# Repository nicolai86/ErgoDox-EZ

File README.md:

# ErgoDox-EZ

[ErgoDox EZ](https://ergodox-ez.com/) LED mod to convert your regular ErgoDox EZ into an ErgoDox EZ shine.  
The total cost for this mod is about about 40 CAD (~30 CAD for PCBs, ~10 CAD for components)

## Instructions

To build this mod you need to assemble two LED strips, and one I2C bridge. The LED strips are installed on both sides. The right hand LED strip is directly connected to the main PCB. The left hand LED strip requires an I2C bridge to function.

## Firmware

Once you've connected your Atmega168 you can compile the firmware and flash your microcontroller with the included makefile:

```
$ make build
$ make flash
```

The makefile is setup to use the AVR ISP MKII.

## LED strip

You will need to LED pcbs to build this mod. The LED strips are identical for both sides.

### List of materials

| Component | Amount        | Notes |
|-----------|:-------------:|------:|
| RGBW6812  | 30            | 15 per side; Can be ordered at Aliexpress |
| 3-pin micro JST connector | 1 | right hand connector to main PCB |

The gerber files, eagle project schematics and board files are included in the led-strip folder.

### Assembly

The LED strip assembly needs to be done twice, once for each half. For each side:

1. Solder all 15 RGBW SK6812 LEDs 
2. Solder the cables according to the marks

For the right hand you can solder the cables to the keyboard, or use a 3-pin micro JST connector instead.
The left hand needs to be connected to an I2C bridge:

## I2C bridge

### List of materials

| Component | Amount        | Notes |
|-----------|:-------------:|------:|
| atmega168pa-au  | 1       | Required to decode I2C traffic |
| 0805 22pF cap   | 2       | |
| 0805 10uF cap   | 1       | |
| 0805 10K resistor | 3     | |
| CSM-7X-DU 16Mhz oscillator | 1     | |
| 6 pin AVR ISP connector | 1     | |
| 4-pin micro JST connector | 1 | left hand connector to main PCB |

The gerber files, eagle project schematics and board files are included in the i2c-bride folder.

## Assembly

1. Solder the Atmega168p. Make sure to align the dark circle with the PCB properly. I've used SMD solder paste to place a film over all pins, solder one pin at a time.
2. Solder the 2 22pF caps, C3 and C2.
3. Solder the oscillator. 
4. Solder the 10uF cap.
5. Solder the 3 10k res.
6. Solder the jack. Note that you'll need to desolder it after flashing, or cut them off.

The left hand will look like this after soldering:

check out [KeebTalk](https://www.keebtalk.com/t/did-anybody-try-to-mod-their-ergodox-ez-with-a-custom-led-array/2286) for more images.

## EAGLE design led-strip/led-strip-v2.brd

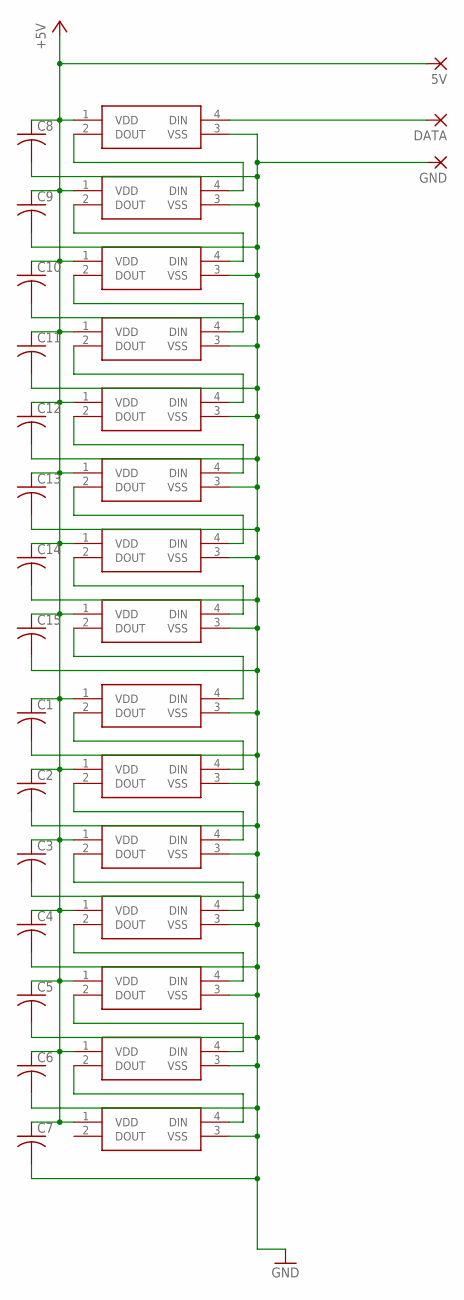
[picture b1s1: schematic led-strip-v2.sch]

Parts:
5V: 1,6/0,8
C1, C2, C3, C4, C5, C6, C7, C8, C9, C10, C11, C12, C13, C14, C15: C-USC0805; C0805
DATA: 1,6/0,8
GND: 1,6/0,8
LED1, LED2, LED3, LED4, LED5, LED6, LED7, LED8, LED9, LED10, LED11, LED12, LED13, LED14, LED15: 1655; WS2812B_1

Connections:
+5V: 5V.1, C1.1, C2.1, C3.1, C4.1, C5.1, C6.1, C7.1, C8.1, C9.1, C10.1, C11.1, C12.1, C13.1, C14.1, C15.1, LED1.1 (VDD), LED2.1 (VDD), LED3.1 (VDD), LED4.1 (VDD), LED5.1 (VDD), LED6.1 (VDD), LED7.1 (VDD), LED8.1 (VDD), LED9.1 (VDD), LED10.1 (VDD), LED11.1 (VDD), LED12.1 (VDD), LED13.1 (VDD), LED14.1 (VDD), LED15.1 (VDD)
DATA-IN: DATA.1, LED1.4 (DIN)
GND: C1.2, C2.2, C3.2, C4.2, C5.2, C6.2, C7.2, C8.2, C9.2, C10.2, C11.2, C12.2, C13.2, C14.2, C15.2, GND.1, LED1.3 (VSS), LED2.3 (VSS), LED3.3 (VSS), LED4.3 (VSS), LED5.3 (VSS), LED6.3 (VSS), LED7.3 (VSS), LED8.3 (VSS), LED9.3 (VSS), LED10.3 (VSS), LED11.3 (VSS), LED12.3 (VSS), LED13.3 (VSS), LED14.3 (VSS), LED15.3 (VSS)
unnamed: LED1.2 (DOUT), LED2.4 (DIN)
unnamed: LED2.2 (DOUT), LED3.4 (DIN)
unnamed: LED3.2 (DOUT), LED4.4 (DIN)
unnamed: LED4.2 (DOUT), LED5.4 (DIN)
unnamed: LED5.2 (DOUT), LED6.4 (DIN)
unnamed: LED6.2 (DOUT), LED7.4 (DIN)
unnamed: LED7.2 (DOUT), LED8.4 (DIN)
unnamed: LED8.2 (DOUT), LED9.4 (DIN)
unnamed: LED9.2 (DOUT), LED10.4 (DIN)
unnamed: LED10.2 (DOUT), LED11.4 (DIN)
unnamed: LED11.2 (DOUT), LED12.4 (DIN)
unnamed: LED12.2 (DOUT), LED13.4 (DIN)
unnamed: LED13.2 (DOUT), LED14.4 (DIN)
unnamed: LED14.2 (DOUT), LED15.4 (DIN)

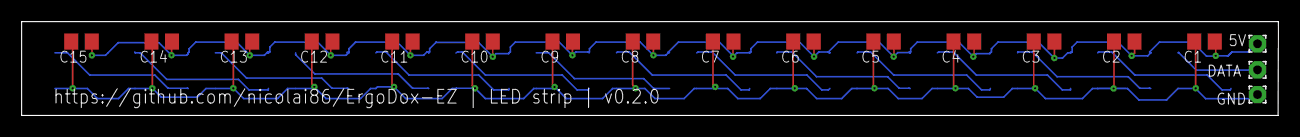
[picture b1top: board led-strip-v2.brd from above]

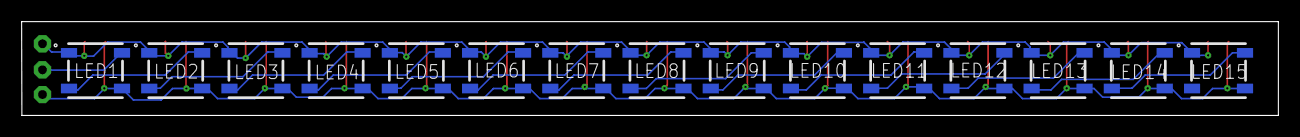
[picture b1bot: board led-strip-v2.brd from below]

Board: 2 copper layers, 116.3 x 8.7 mm, 33 parts (15 on the bottom side), 17 nets.

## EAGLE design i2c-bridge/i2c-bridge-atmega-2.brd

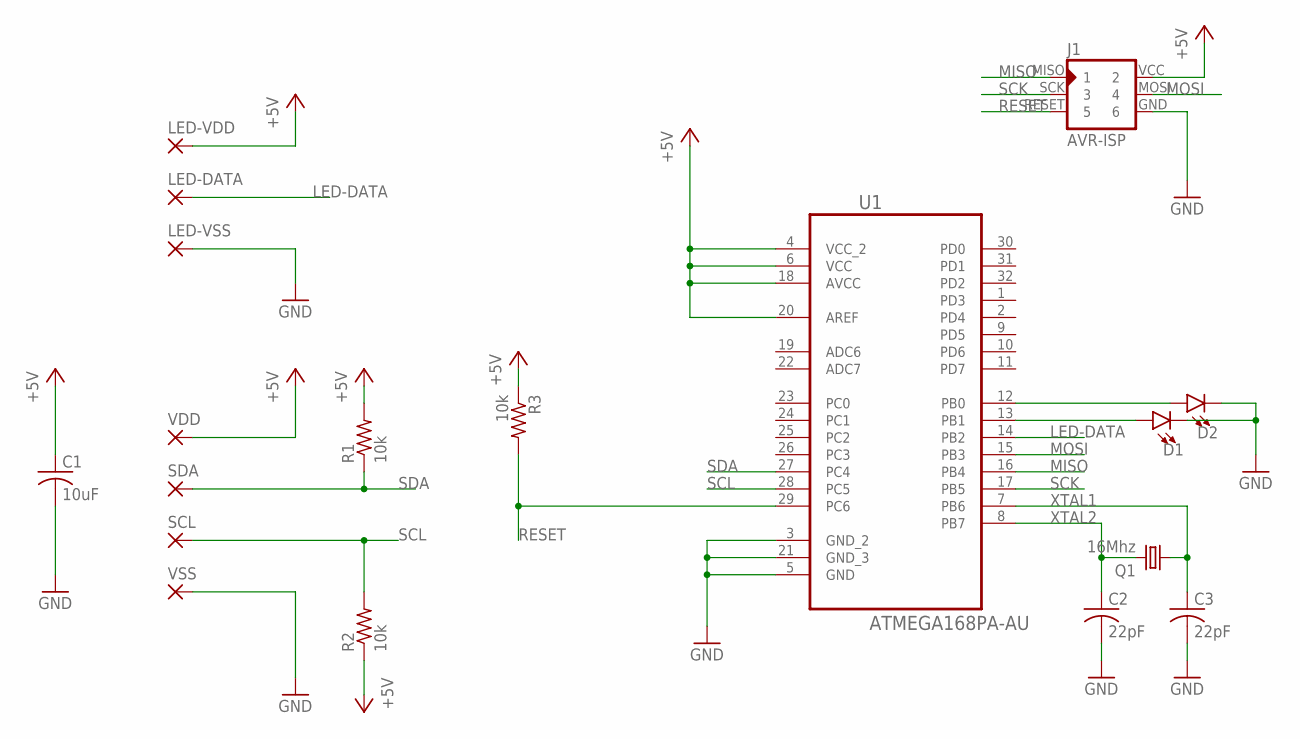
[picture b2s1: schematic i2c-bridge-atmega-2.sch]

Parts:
C1: 10uF; C0805
C2, C3: 22pF; C0805
D1, D2: WHITE; LED-1206
J1: AVR-ISP; AVR-ISP-6PIN-SMAILL-SILK
LED-DATA: SMD2; SMD1,27-2,54
LED-VDD: SMD2; SMD1,27-2,54
LED-VSS: SMD2; SMD1,27-2,54
Q1: 16Mhz; CSM-7X-DU
R1, R2, R3: 10k; R0805
SCL: SMD2; SMD1,27-2,54
SDA: SMD2; SMD1,27-2,54
U1: ATMEGA168PA-AU; QFP80P900X900X120-32N
VDD: SMD2; SMD1,27-2,54
VSS: SMD2; SMD1,27-2,54

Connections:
+5V: C1.1, J1.VCC (2), LED-VDD.1, R1.2, R2.1, R3.1, U1.4 (VCC_2), U1.6 (VCC), U1.18 (AVCC), U1.20 (AREF), VDD.1
GND: C1.2, C2.2, C3.2, D1.C, D2.C, J1.GND (6), LED-VSS.1, U1.3 (GND_2), U1.5 (GND), U1.21 (GND_3), VSS.1
LED-DATA: LED-DATA.1, U1.14 (PB2)
MISO: J1.MISO (1), U1.16 (PB4)
MOSI: J1.MOSI (4), U1.15 (PB3)
unnamed: D1.A, U1.13 (PB1)
unnamed: D2.A, U1.12 (PB0)
RESET: J1.RESET (5), R3.2, U1.29 (PC6)
SCK: J1.SCK (3), U1.17 (PB5)
SCL: R2.2, SCL.1, U1.28 (PC5)
SDA: R1.1, SDA.1, U1.27 (PC4)
XTAL1: C3.1, Q1.1, U1.7 (PB6)
XTAL2: C2.1, Q1.2, U1.8 (PB7)

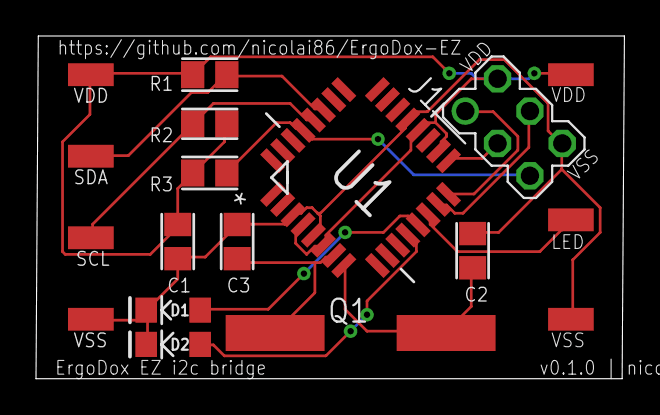
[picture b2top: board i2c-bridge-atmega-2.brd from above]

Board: 2 copper layers, 32.7 x 19.0 mm, 18 parts (0 on the bottom side), 13 nets.

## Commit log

2018-10-12 add atmega168 i2c source
    the atmega168 acts as the FPGA used in the original ErgoDox EZ shine.
    It reads the RGBW data via I2C and sets it to the LEDs once all data is
    received.
2018-10-13 add makefile for atmega firmware mgmt
2018-10-13 add eagle project files and gerber exports
2018-10-27 update makefile for SMD PCB
    the SMD one uses the atmega168p
2018-10-27 add assembly instructions
2018-10-27 include estimate about total costs
2019-02-01 add v0.2.0 with decoupling capacitors between leds
2019-09-11 add schematic

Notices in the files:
parts and their libraries:
SparkFun-LED: Licensing: Creative Commons ShareAlike 4.0 International - https://creativecommons.org/licenses/by-sa/4.0
